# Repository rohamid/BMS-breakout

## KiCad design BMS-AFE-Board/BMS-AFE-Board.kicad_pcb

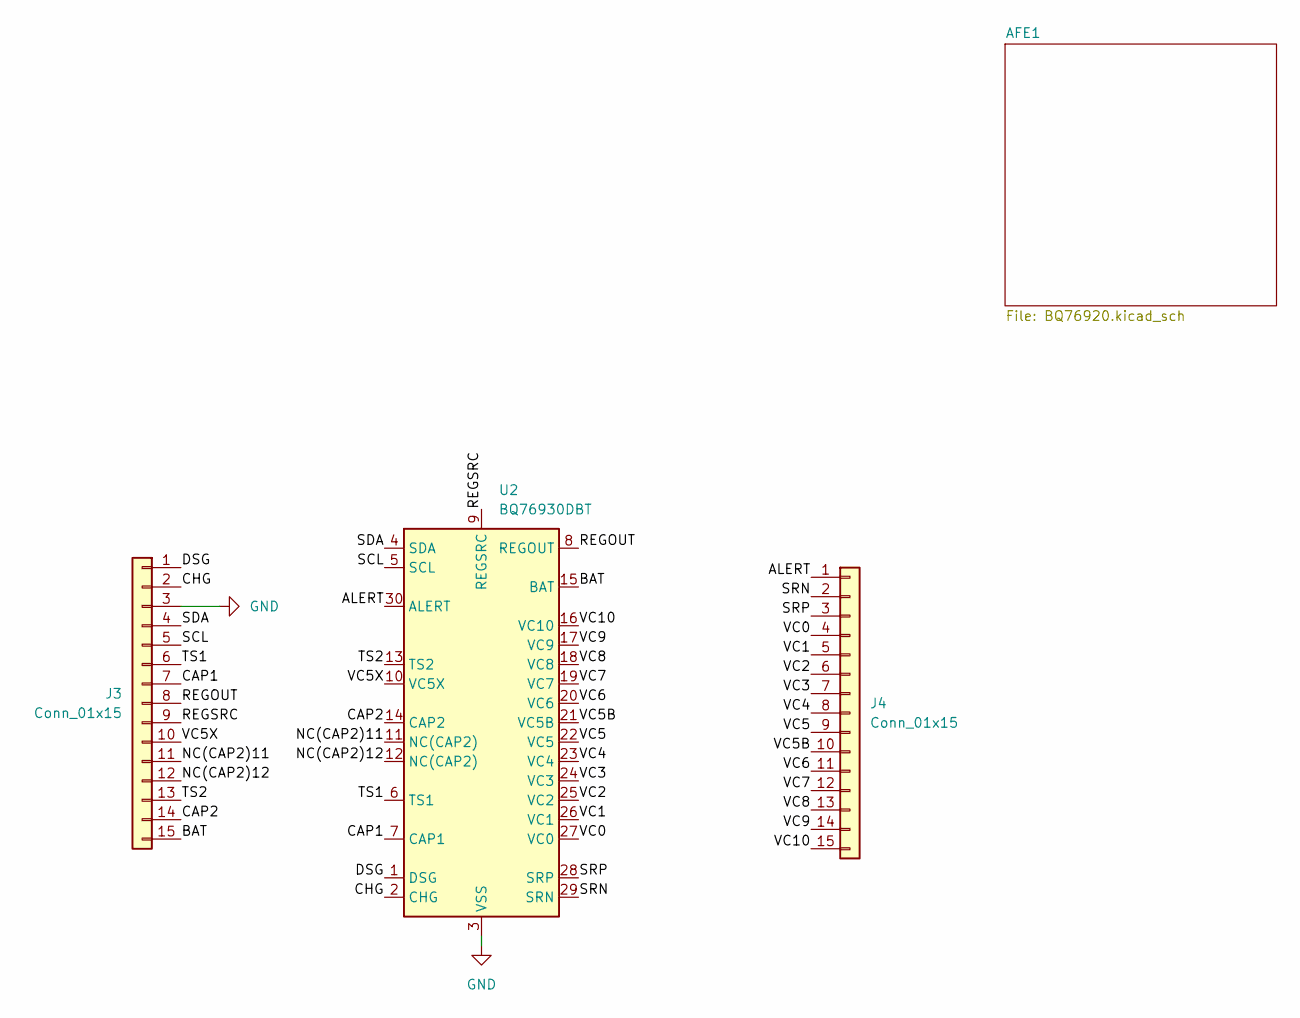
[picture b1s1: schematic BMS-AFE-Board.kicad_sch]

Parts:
J3, J4: Conn_01x15; PinHeader_1x15_P2.54mm_Vertical
U2: BQ76930DBT; TSSOP-30_4.4x7.8mm_P0.5mm

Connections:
/ALERT: J4.1, U2.30 (ALERT)
/BAT: J3.15, U2.15 (BAT)
/CAP1: J3.7, U2.7 (CAP1)
/CAP2: J3.14, U2.14 (CAP2)
/CHG: J3.2, U2.2 (CHG)
/DSG: J3.1, U2.1 (DSG)
/NC(CAP2)11: J3.11, U2.11 (NC(CAP2))
/NC(CAP2)12: J3.12, U2.12 (NC(CAP2))
/REGOUT: J3.8, U2.8 (REGOUT)
/REGSRC: J3.9, U2.9 (REGSRC)
/SCL: J3.5, U2.5 (SCL)
/SDA: J3.4, U2.4 (SDA)
/SRN: J4.2, U2.29 (SRN)
/SRP: J4.3, U2.28 (SRP)
/TS1: J3.6, U2.6 (TS1)
/TS2: J3.13, U2.13 (TS2)
/VC0: J4.4, U2.27 (VC0)
/VC1: J4.5, U2.26 (VC1)
/VC2: J4.6, U2.25 (VC2)
/VC3: J4.7, U2.24 (VC3)
/VC4: J4.8, U2.23 (VC4)
/VC5: J4.9, U2.22 (VC5)
/VC5B: J4.10, U2.21 (VC5B)
/VC5X: J3.10, U2.10 (VC5X)
/VC6: J4.11, U2.20 (VC6)
/VC7: J4.12, U2.19 (VC7)
/VC8: J4.13, U2.18 (VC8)
/VC9: J4.14, U2.17 (VC9)
/VC10: J4.15, U2.16 (VC10)
GND: J3.3, U2.3 (VSS); also elsewhere on the board

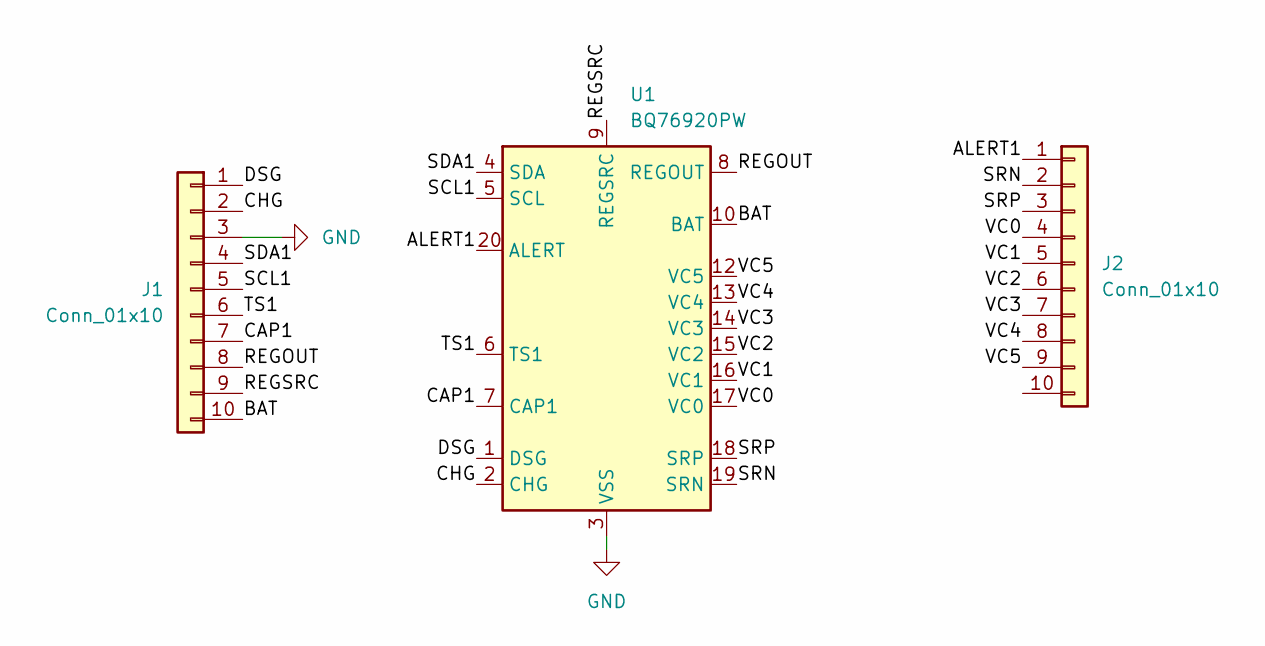
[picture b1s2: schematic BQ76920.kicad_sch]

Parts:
J1, J2: Conn_01x10; PinHeader_1x10_P2.54mm_Vertical
U1: BQ76920PW; TSSOP-20_4.4x6.5mm_P0.65mm

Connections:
/AFE1/ALERT1: J2.1, U1.20 (ALERT)
/AFE1/BAT: J1.10, U1.10 (BAT)
/AFE1/CAP1: J1.7, U1.7 (CAP1)
/AFE1/CHG: J1.2, U1.2 (CHG)
/AFE1/DSG: J1.1, U1.1 (DSG)
/AFE1/REGOUT: J1.8, U1.8 (REGOUT)
/AFE1/REGSRC: J1.9, U1.9 (REGSRC)
/AFE1/SCL1: J1.5, U1.5 (SCL)
/AFE1/SDA1: J1.4, U1.4 (SDA)
/AFE1/SRN: J2.2, U1.19 (SRN)
/AFE1/SRP: J2.3, U1.18 (SRP)
/AFE1/TS1: J1.6, U1.6 (TS1)
/AFE1/VC0: J2.4, U1.17 (VC0)
/AFE1/VC1: J2.5, U1.16 (VC1)
/AFE1/VC2: J2.6, U1.15 (VC2)
/AFE1/VC3: J2.7, U1.14 (VC3)
/AFE1/VC4: J2.8, U1.13 (VC4)
/AFE1/VC5: J2.9, U1.12 (VC5)
GND: J1.3, U1.3 (VSS); also elsewhere on the board

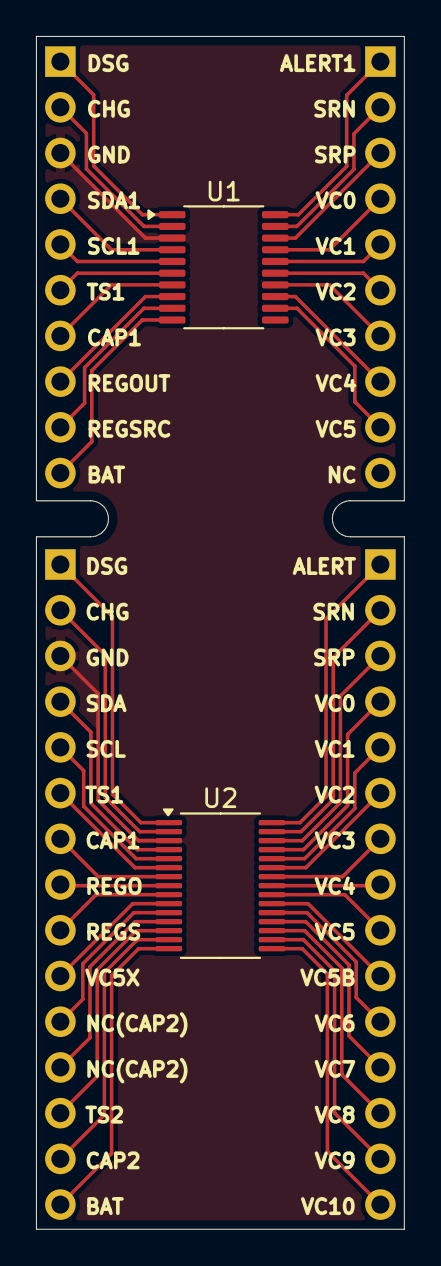
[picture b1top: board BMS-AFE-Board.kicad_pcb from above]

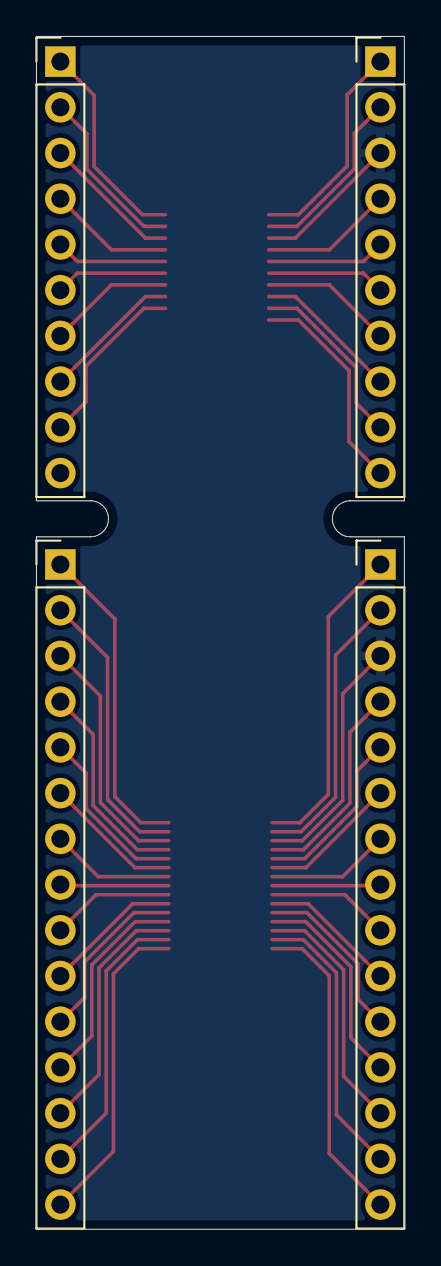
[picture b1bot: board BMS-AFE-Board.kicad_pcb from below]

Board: 2 copper layers, 20.4 x 66.3 mm, 6 parts (4 on the bottom side), 48 nets.

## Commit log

2025-01-13 Finished tracks, ground via left
